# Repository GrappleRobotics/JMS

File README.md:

JMS
===
Another alternative Field Management System for the FIRST Robotics Competition.

JMS is based heavily off the official FRC FMS, as well as Cheesy-Arena. JMS differs in that the bulk of the network operations are performed onboard the JMS server itself, requiring minimal external and increasing the reliability of the system.

For those early-birds, do NOT install this on your personal machine. JMS WILL override your network, dhcp, and firewall settings. JMS is designed to be run on a Ubuntu Server 20.04 instance (either physical or in a VM).

More information coming soon.

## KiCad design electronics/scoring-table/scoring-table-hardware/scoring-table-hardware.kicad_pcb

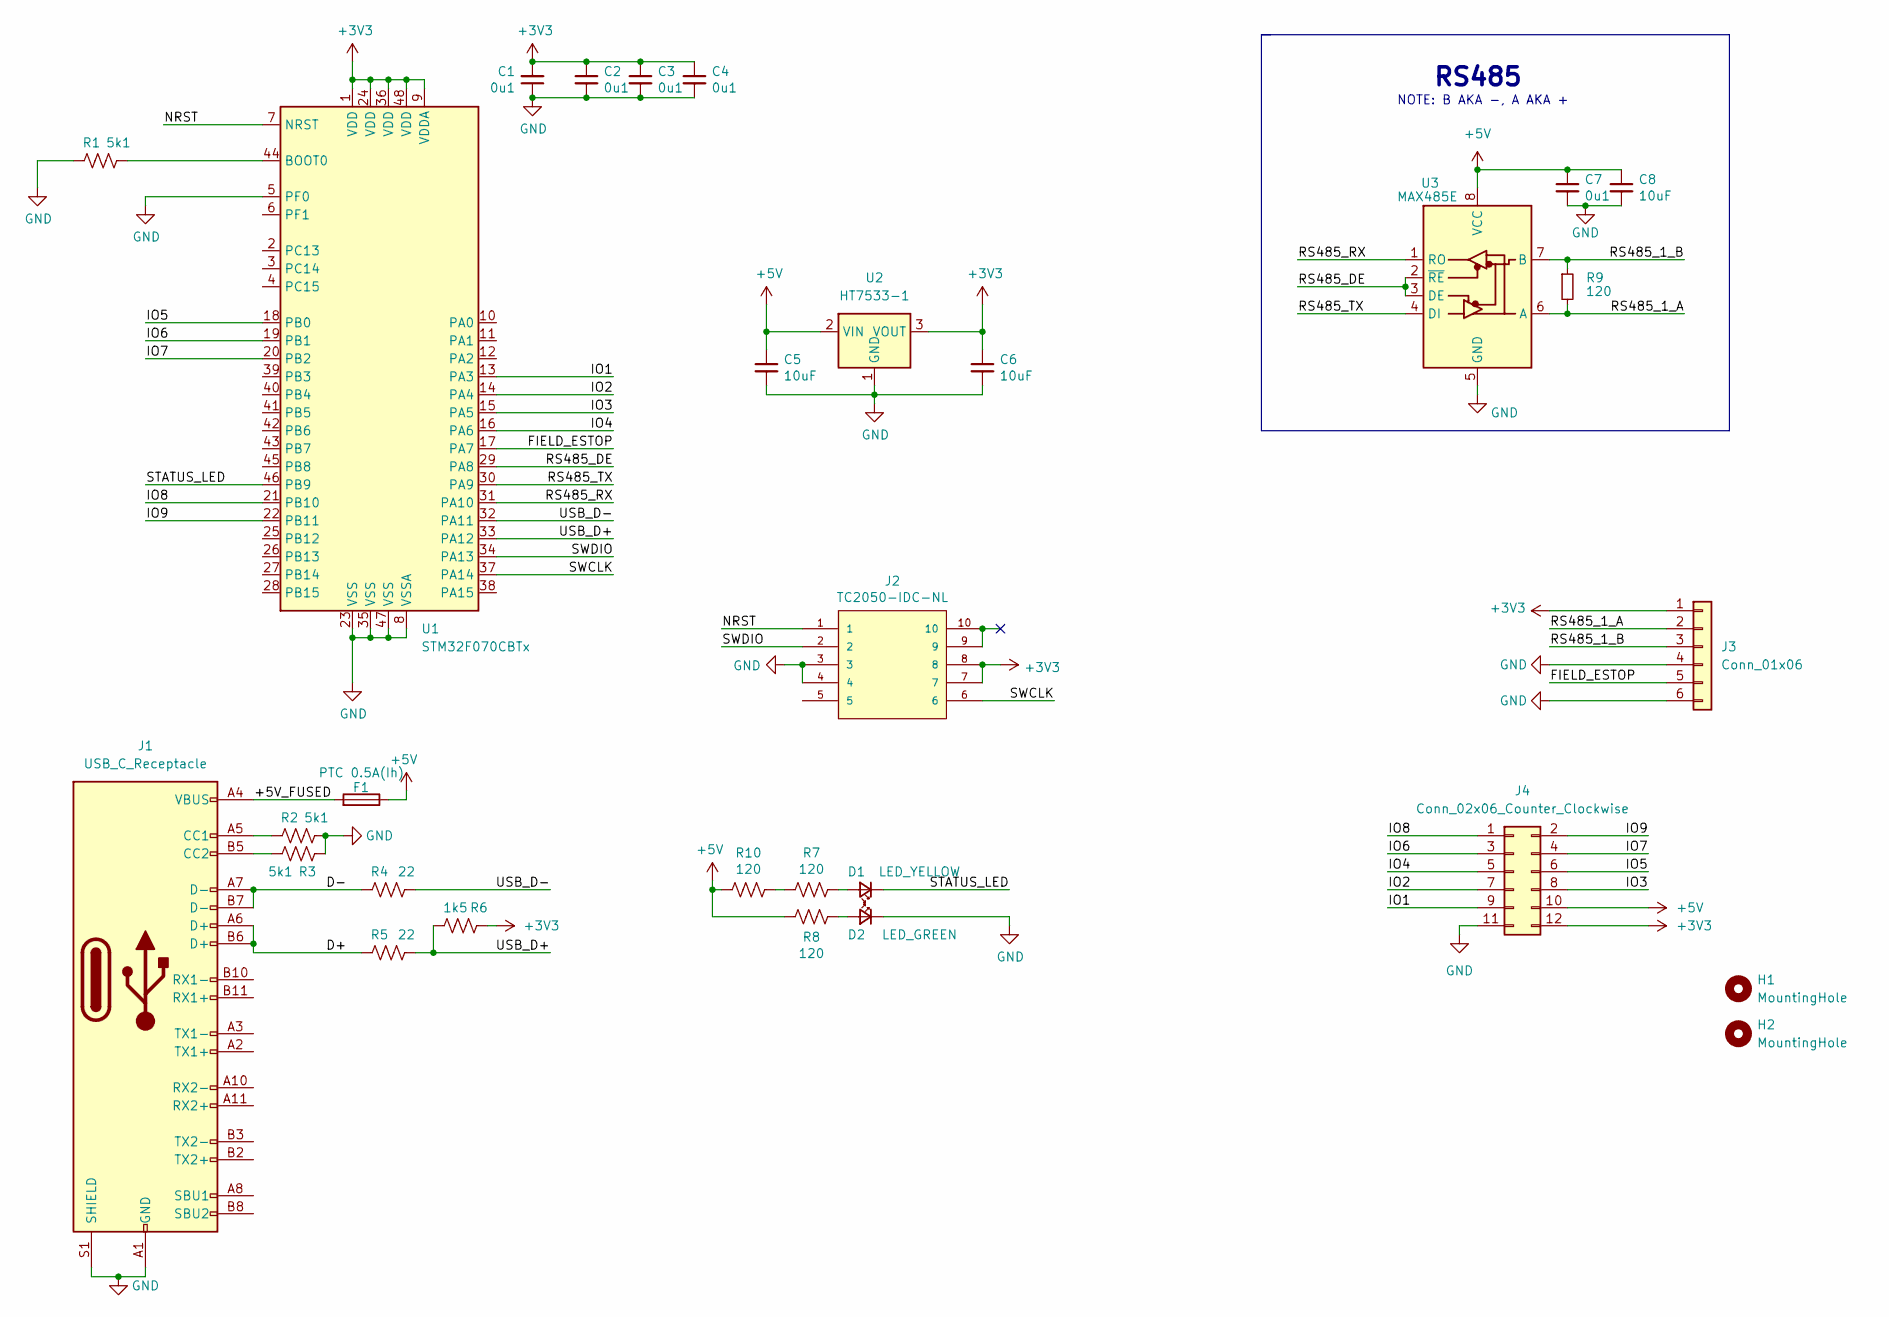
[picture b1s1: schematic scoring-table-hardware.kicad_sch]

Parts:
C1, C2, C3, C4, C7: 0u1; C_0603_1608Metric; LCSC C14663
C5, C6, C8: 10uF; C_0603_1608Metric; LCSC C96446
D1: LED_YELLOW; LED_0603_1608Metric; LCSC C72038
D2: LED_GREEN; LED_0603_1608Metric; LCSC C72043
F1: PTC 0.5A(Ih); Fuse_1206_3216Metric; LCSC C883126
H1, H2: MountingHole; MountingHole_3.2mm_M3
J1: USB_C_Receptacle; USB_C_Receptacle_Molex_105450-0101; LCSC C134092
J2: TC2050-IDC-NL; TAG-CONNECT_TC2050-IDC-NL; PARTREV A
J3: Conn_01x06; PhoenixContact_MC_1,5_6-G-5.08_1x06_P5.08mm_Horizontal; LCSC C505828
J4: Conn_02x06_Counter_Clockwise; PinHeader_2x06_P2.54mm_Vertical
R1, R2, R3: 5k1; R_0603_1608Metric; LCSC C23186
R4, R5: 22; R_0603_1608Metric; LCSC C23345
R6: 1k5; R_0603_1608Metric; LCSC C22843
R7, R8, R9, R10: 120; R_0603_1608Metric; LCSC C22787
U1: STM32F070CBTx; LQFP-48_7x7mm_P0.5mm; LCSC C74909
U2: HT7533-1; SOT-89-3; LCSC C14289
U3: MAX485E; SOIC-8_3.9x4.9mm_P1.27mm; LCSC C19738

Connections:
+3V3: C1.2, C2.1, C3.1, C4.1, C6.1, J2.7, J2.8, J3.1, J4.12, R6.2, U1.1 (VDD), U1.9 (VDDA), U1.24 (VDD), U1.36 (VDD), U1.48 (VDD), U2.3 (VOUT)
+5V: C5.1, C7.1, C8.1, F1.1, J4.10, R8.1, R10.1, U2.2 (VIN), U3.8 (VCC)
/+5V_FUSED: F1.2, J1.A4 (VBUS), J1.A9 (VBUS), J1.B4 (VBUS), J1.B9 (VBUS)
/D+: J1.A6 (D+), J1.B6 (D+), R5.2
/D-: J1.A7 (D-), J1.B7 (D-), R4.2
/FIELD_ESTOP: J3.5, U1.17 (PA7)
/IO1: J4.9, U1.13 (PA3)
/IO2: J4.7, U1.14 (PA4)
/IO3: J4.8, U1.15 (PA5)
/IO4: J4.5, U1.16 (PA6)
/IO5: J4.6, U1.18 (PB0)
/IO6: J4.3, U1.19 (PB1)
/IO7: J4.4, U1.20 (PB2)
/IO8: J4.1, U1.21 (PB10)
/IO9: J4.2, U1.22 (PB11)
/NRST: J2.1, U1.7 (NRST)
/RS485_1_A: J3.2, R9.2, U3.6 (A)
/RS485_1_B: J3.3, R9.1, U3.7 (B)
/RS485_DE: U1.29 (PA8), U3.2 (~RE), U3.3 (DE)
/RS485_RX: U1.31 (PA10), U3.1 (RO)
/RS485_TX: U1.30 (PA9), U3.4 (DI)
/STATUS_LED: D1.1 (K), U1.46 (PB9)
/SWCLK: J2.6, U1.37 (PA14)
/SWDIO: J2.2, U1.34 (PA13)
/USB_D+: R5.1, R6.1, U1.33 (PA12)
/USB_D-: R4.1, U1.32 (PA11)
GND: C1.1, C2.2, C3.2, C4.2, C5.2, C6.2, C7.2, C8.2, D2.1 (K), J1.A1 (GND), J1.A12 (GND), J1.B1 (GND), J1.B12 (GND), J1.S1 (SHIELD), J2.3, J2.4, J3.4, J3.6, J4.11, R1.2, R2.1, R3.2, U1.5 (PF0), U1.8 (VSSA), U1.23 (VSS), U1.35 (VSS), U1.47 (VSS), U2.1 (GND), U3.5 (GND)
unnamed: J1.A5 (CC1), R2.2
unnamed: J1.B5 (CC2), R3.1
unnamed: R7.1, R10.2
unnamed: D1.2 (A), R7.2
unnamed: D2.2 (A), R8.2
unnamed: R1.1, U1.44 (BOOT0)

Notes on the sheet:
RS485
NOTE: B AKA -, A AKA +

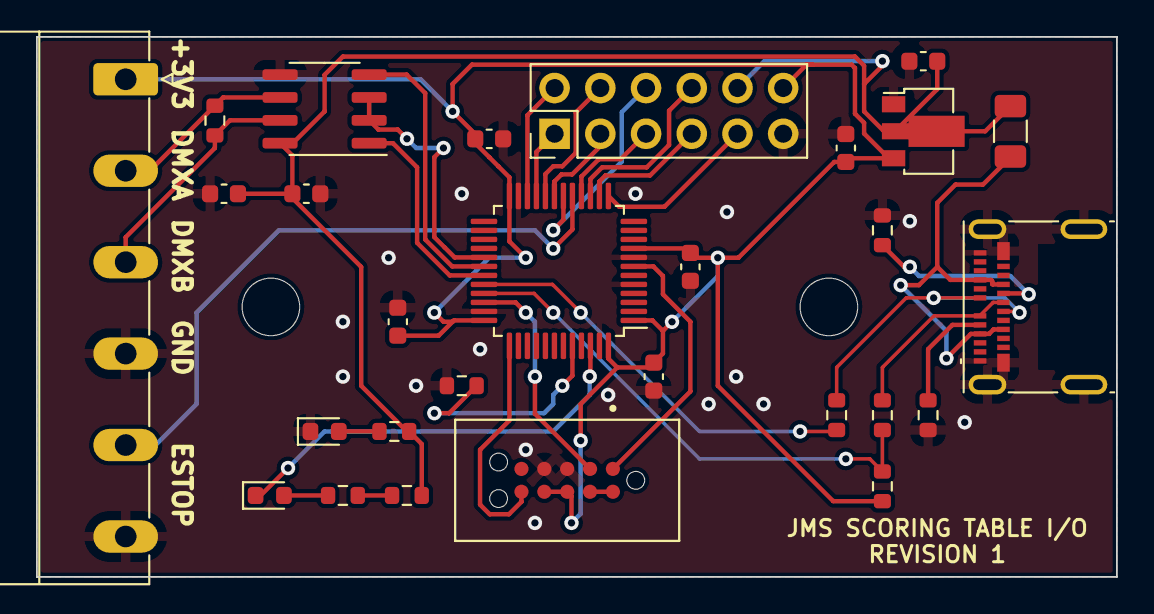
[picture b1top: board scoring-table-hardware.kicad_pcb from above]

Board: 2 copper layers, 60.0 x 30.0 mm, 30 parts (0 on the bottom side), 33 nets.

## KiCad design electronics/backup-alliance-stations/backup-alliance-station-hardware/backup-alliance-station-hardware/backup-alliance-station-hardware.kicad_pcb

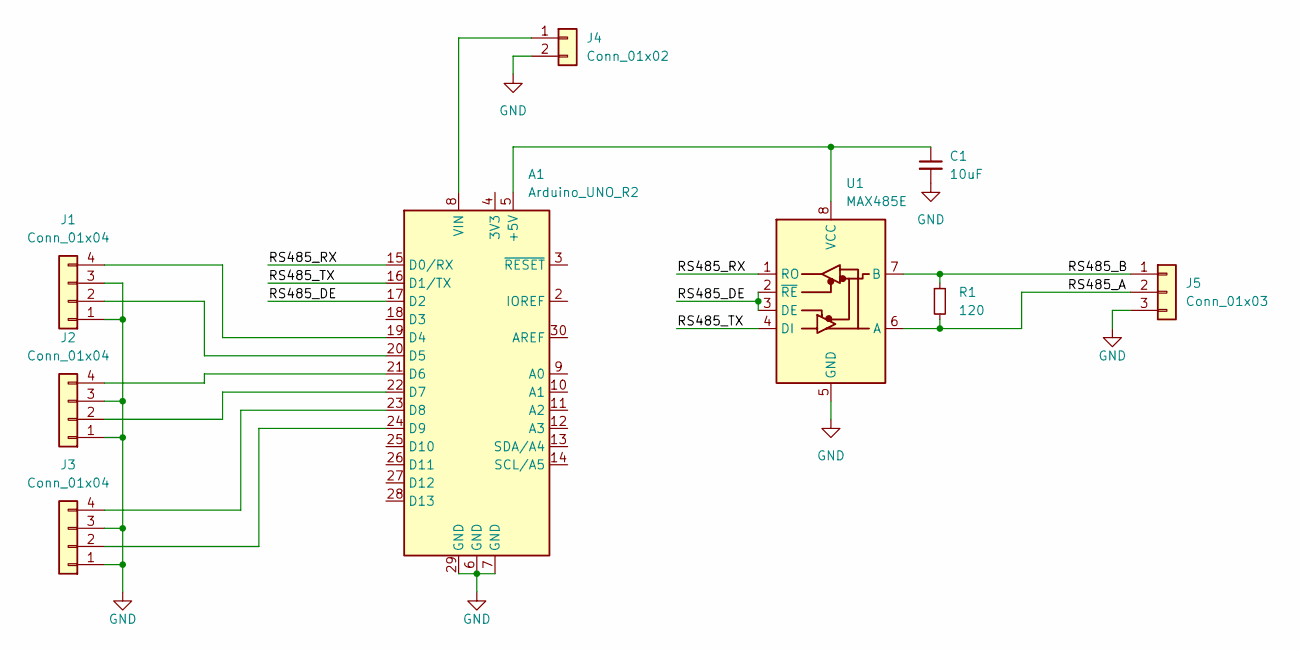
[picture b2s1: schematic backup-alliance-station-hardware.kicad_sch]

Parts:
A1: Arduino_UNO_R2
C1: 10uF; C_Disc_D4.7mm_W2.5mm_P5.00mm
J1, J2, J3: Conn_01x04; TerminalBlock_Phoenix_PT-1,5-4-3.5-H_1x04_P3.50mm_Horizontal
J4: Conn_01x02; TerminalBlock_Phoenix_PT-1,5-2-3.5-H_1x02_P3.50mm_Horizontal
J5: Conn_01x03; TerminalBlock_Phoenix_PT-1,5-3-3.5-H_1x03_P3.50mm_Horizontal
R1: 120; R_Axial_DIN0207_L6.3mm_D2.5mm_P7.62mm_Horizontal
U1: MAX485E; DIP-8_W7.62mm

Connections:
/RS485_A: J5.2, R1.2, U1.6 (A)
/RS485_B: J5.1, R1.1, U1.7 (B)
/RS485_DE: A1.17 (D2), U1.2 (~RE), U1.3 (DE)
/RS485_RX: A1.15 (D0/RX), U1.1 (RO)
/RS485_TX: A1.16 (D1/TX), U1.4 (DI)
GND: A1.6 (GND), A1.7 (GND), A1.29 (GND), C1.2, J1.1, J1.3, J2.1, J2.3, J3.1, J3.3, J4.2, J5.3, U1.5 (GND)
unnamed: A1.5 (+5V), C1.1, U1.8 (VCC)
unnamed: A1.8 (VIN), J4.1
unnamed: A1.19 (D4), J1.4
unnamed: A1.20 (D5), J1.2
unnamed: A1.21 (D6), J2.4
unnamed: A1.22 (D7), J2.2
unnamed: A1.23 (D8), J3.4
unnamed: A1.24 (D9), J3.2

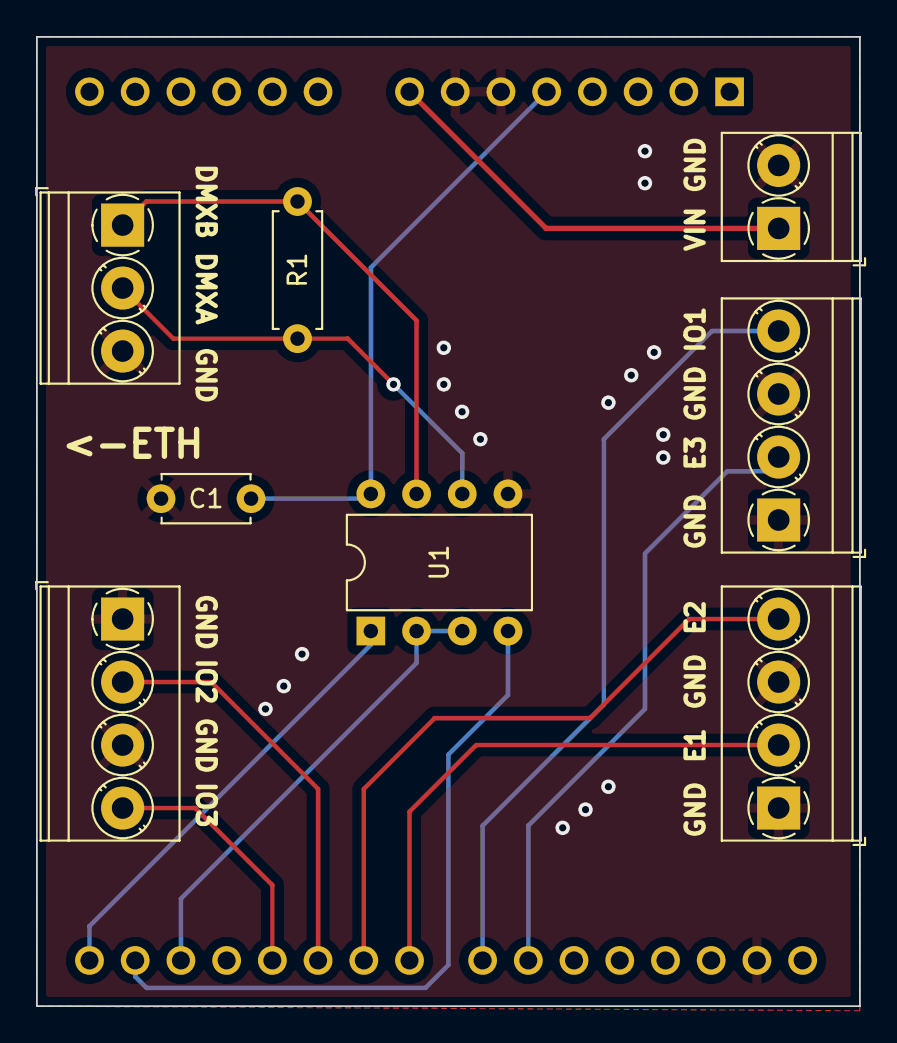
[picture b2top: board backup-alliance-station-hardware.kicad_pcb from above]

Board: 2 copper layers, 45.7 x 53.8 mm, 9 parts (1 on the bottom side), 14 nets.

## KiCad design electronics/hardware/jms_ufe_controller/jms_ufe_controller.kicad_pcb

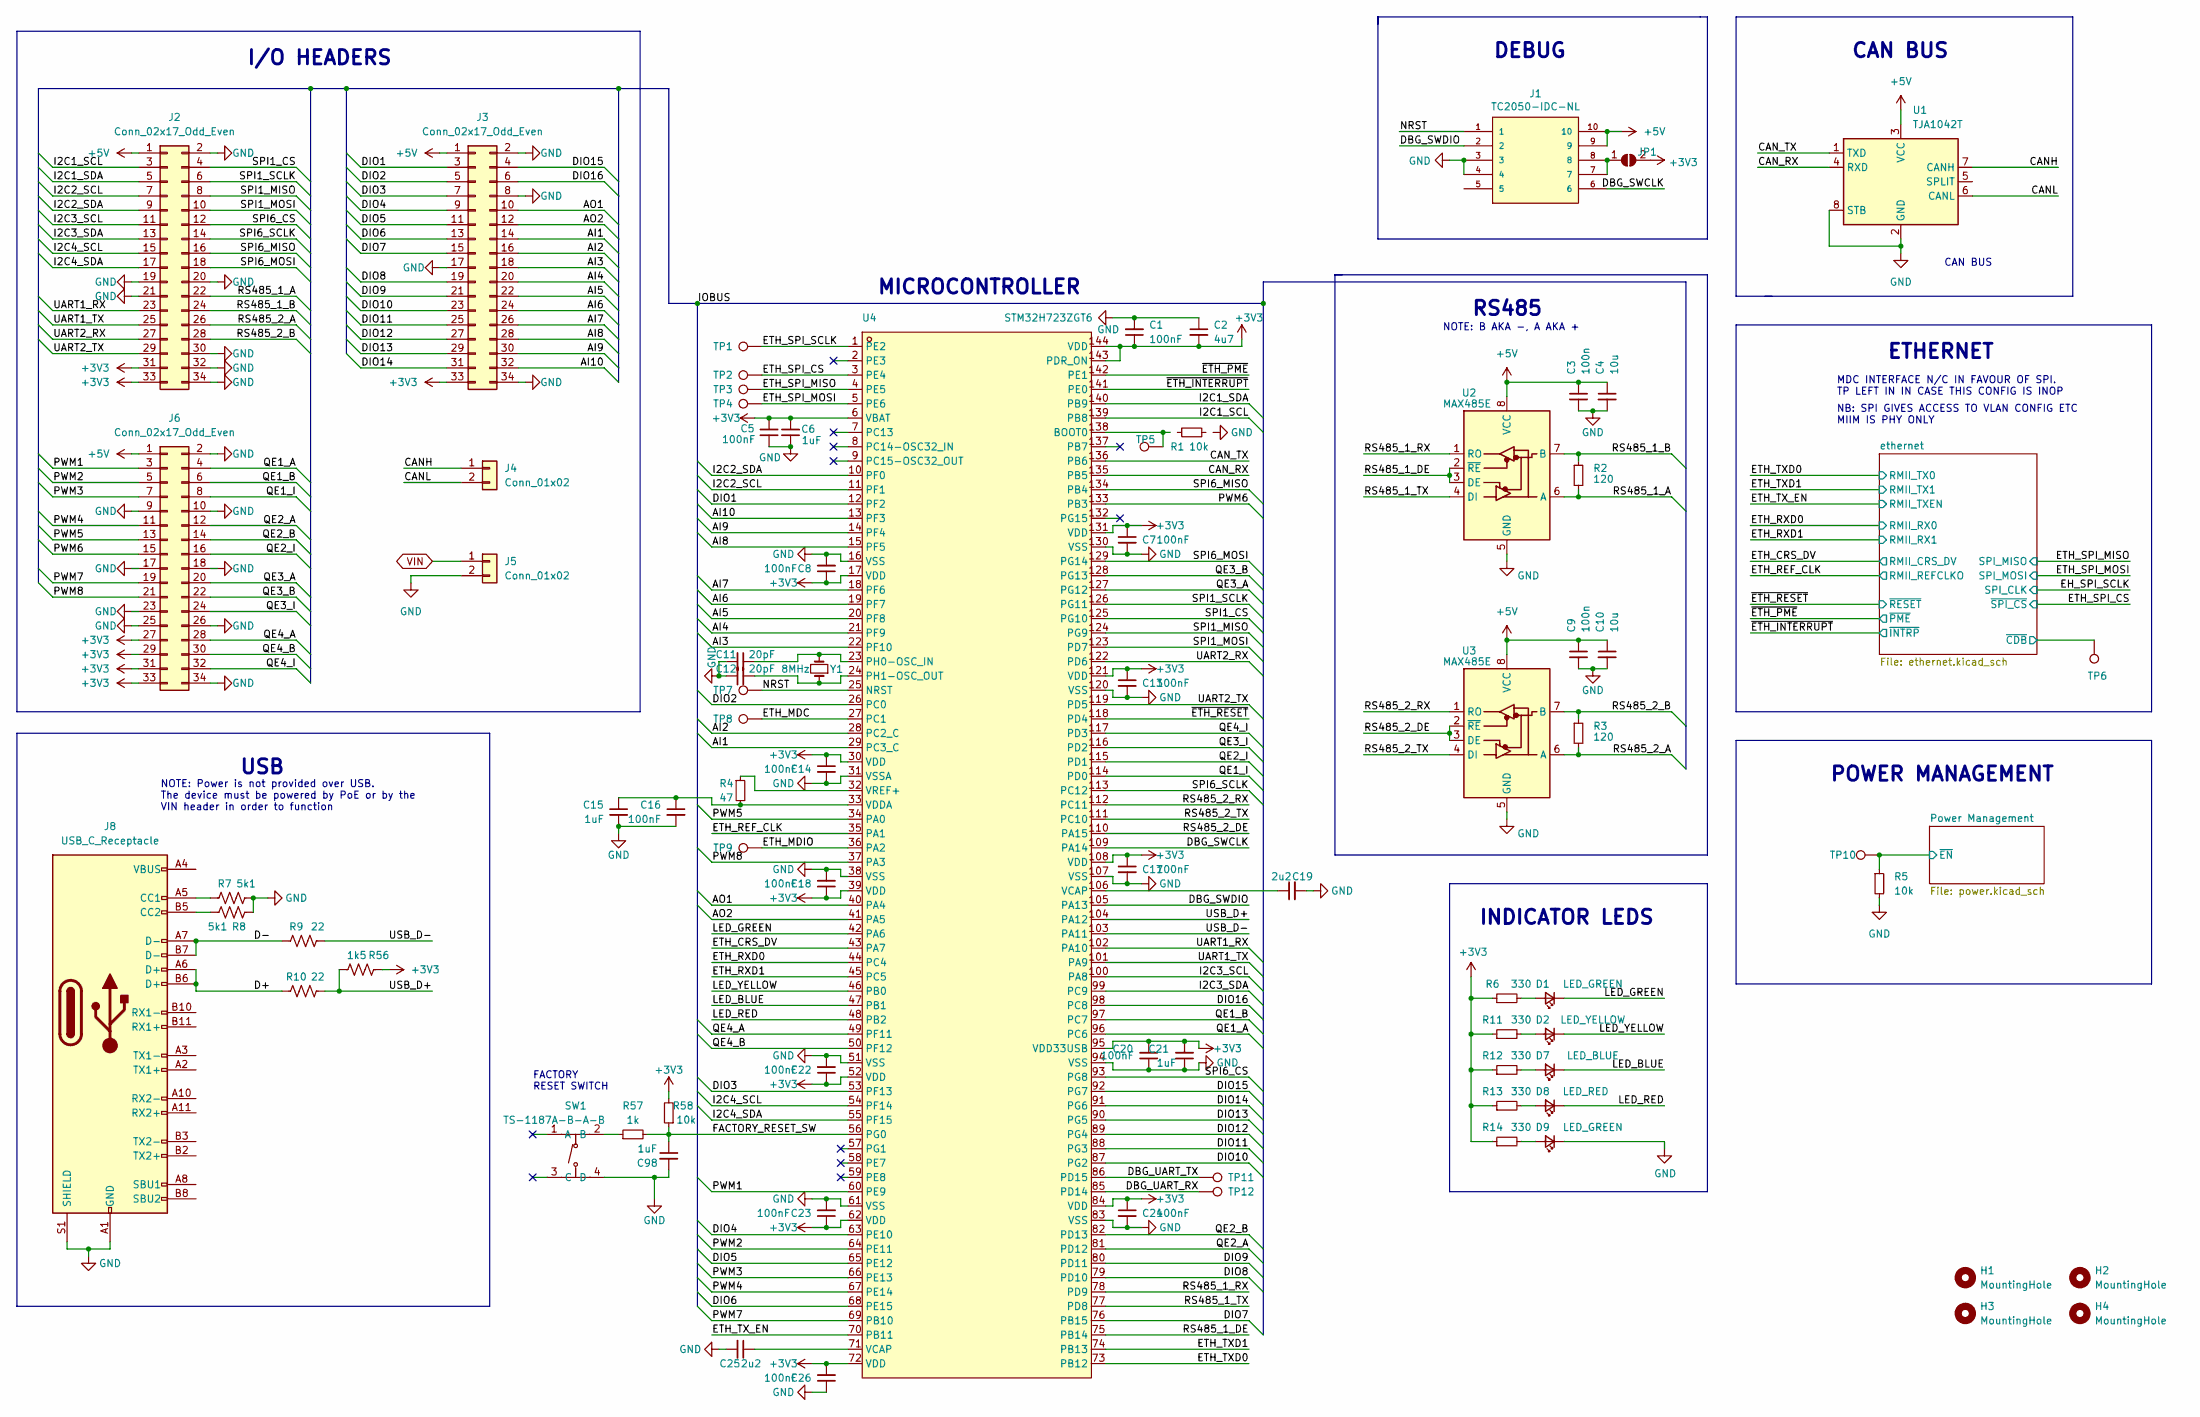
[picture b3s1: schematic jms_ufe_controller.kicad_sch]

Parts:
C1, C5, C7, C8, C13, C14, C16, C17, C18, C20, C22, C23, C24, C26: 100nF; C_0402_1005Metric
C2: 4u7; C_0402_1005Metric
C3, C9: 100n; C_0402_1005Metric
C4, C10: 10u; C_0402_1005Metric
C6, C15, C21, C98: 1uF; C_0402_1005Metric
C11, C12: 20pF; C_0402_1005Metric
C19, C25: 2u2; C_0402_1005Metric
D1, D9: LED_GREEN; LED_0603_1608Metric; LCSC C72043
D2: LED_YELLOW; LED_0603_1608Metric; LCSC C72038
D7: LED_BLUE; LED_0603_1608Metric; LCSC C72041
D8: LED_RED; LED_0603_1608Metric; LCSC C2286
H1, H2, H3, H4: MountingHole; MountingHole_3.2mm_M3
J1: TC2050-IDC-NL; TAG-CONNECT_TC2050-IDC-NL; PARTREV A
J2, J3, J6: Conn_02x17_Odd_Even; PinHeader_2x17_P2.54mm_Vertical
J4, J5: Conn_01x02; TerminalBlock_Phoenix_PT-1,5-2-3.5-H_1x02_P3.50mm_Horizontal
J8: USB_C_Receptacle; USB_C_Receptacle_Molex_105450-0101
JP1: SolderJumper_2_Open; SolderJumper-2_P1.3mm_Open_TrianglePad1.0x1.5mm
R1, R5, R58: 10k; R_0402_1005Metric
R2, R3: 120; R_0402_1005Metric
R4: 47; R_0402_1005Metric
R6, R11, R12, R13, R14: 330; R_0402_1005Metric
R7, R8: 5k1; R_0402_1005Metric
R9, R10: 22; R_0402_1005Metric
R56: 1k5; R_0402_1005Metric
R57: 1k; R_0402_1005Metric
SW1: TS-1187A-B-A-B; SW-SMD_4P-L5.1-W5.1-P3.70-LS6.5-TL-2; LCSC Part C318884
TP1, TP2, TP3, TP4, TP5, TP6, TP7, TP8, TP9, TP10, TP11, TP12: TestPoint; TestPoint_Pad_1.5x1.5mm
U1: TJA1042T; SOIC-8_3.9x4.9mm_P1.27mm; LCSC C53670
U2, U3: MAX485E; SOIC-8_3.9x4.9mm_P1.27mm; LCSC C19738
U4: STM32H723ZGT6; LQFP-144_L20.0-W20.0-P0.50-LS22.0-BL; LCSC Part C730146
Y1: 8MHz; Crystal_SMD_5032-2Pin_5.0x3.2mm; LCSC C115962

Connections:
+3V3: C1.1, C2.2, C5.2, C6.2, C7.1, C8.1, C13.1, C14.1, C17.1, C18.1, C20.2, C21.2, C22.1, C23.1, C24.1, C26.2, J2.31, J2.33, J3.33, J6.27, J6.29, J6.31, J6.33, JP1.2 (B), R6.1, R11.1, R12.1, R13.1, R14.1, R56.2, R58.2, U4.6 (VBAT), U4.17 (VDD), U4.30 (VDD), U4.39 (VDD), U4.52 (VDD), U4.62 (VDD), U4.72 (VDD), U4.84 (VDD), U4.95 (VDD33USB), U4.108 (VDD), U4.121 (VDD), U4.131 (VDD), U4.143 (PDR_ON), U4.144 (VDD); also elsewhere on the board
+5V: C3.1, C4.1, C9.1, C10.1, J1.9, J1.10, J2.1, J3.1, J6.1, U1.3 (VCC), U2.8 (VCC), U3.8 (VCC); also elsewhere on the board
/AI1: J3.14, U4.29 (PC3_C)
/AI2: J3.16, U4.28 (PC2_C)
/AI3: J3.18, U4.22 (PF10)
/AI4: J3.20, U4.21 (PF9)
/AI5: J3.22, U4.20 (PF8)
/AI6: J3.24, U4.19 (PF7)
/AI7: J3.26, U4.18 (PF6)
/AI8: J3.28, U4.15 (PF5)
/AI9: J3.30, U4.14 (PF4)
/AI10: J3.32, U4.13 (PF3)
/AO1: J3.10, U4.40 (PA4)
/AO2: J3.12, U4.41 (PA5)
/CANH: J4.1, U1.7 (CANH)
/CANL: J4.2, U1.6 (CANL)
/CAN_RX: U1.4 (RXD), U4.135 (PB5)
/CAN_TX: U1.1 (TXD), U4.136 (PB6)
/D+: J8.A6 (D+), J8.B6 (D+), R10.2
/D-: J8.A7 (D-), J8.B7 (D-), R9.2
/DBG_SWCLK: J1.6, U4.109 (PA14)
/DBG_SWDIO: J1.2, U4.105 (PA13)
/DBG_UART_RX: TP12.1, U4.85 (PD14)
/DBG_UART_TX: TP11.1, U4.86 (PD15)
/DIO1: J3.3, U4.12 (PF2)
/DIO2: J3.5, U4.26 (PC0)
/DIO3: J3.7, U4.53 (PF13)
/DIO4: J3.9, U4.63 (PE10)
/DIO5: J3.11, U4.65 (PE12)
/DIO6: J3.13, U4.68 (PE15)
/DIO7: J3.15, U4.76 (PB15)
/DIO8: J3.19, U4.79 (PD10)
/DIO9: J3.21, U4.80 (PD11)
/DIO10: J3.23, U4.87 (PG2)
/DIO11: J3.25, U4.88 (PG3)
/DIO12: J3.27, U4.89 (PG4)
/DIO13: J3.29, U4.90 (PG5)
/DIO14: J3.31, U4.91 (PG6)
/DIO15: J3.4, U4.92 (PG7)
/DIO16: J3.6, U4.98 (PC8)
/ETH_CRS_DV: U4.43 (PA7); also elsewhere on the board
/ETH_MDC: TP8.1, U4.27 (PC1)
/ETH_MDIO: TP9.1, U4.36 (PA2)
/ETH_REF_CLK: U4.35 (PA1); also elsewhere on the board
/ETH_RXD0: U4.44 (PC4); also elsewhere on the board
/ETH_RXD1: U4.45 (PC5); also elsewhere on the board
/ETH_SPI_CS: TP2.1, U4.3 (PE4); also elsewhere on the board
/ETH_SPI_MISO: TP3.1, U4.4 (PE5); also elsewhere on the board
/ETH_SPI_MOSI: TP4.1, U4.5 (PE6); also elsewhere on the board
/ETH_SPI_SCLK: TP1.1, U4.1 (PE2)
/ETH_TXD0: U4.73 (PB12); also elsewhere on the board
/ETH_TXD1: U4.74 (PB13); also elsewhere on the board
/ETH_TX_EN: U4.70 (PB11); also elsewhere on the board
/FACTORY_RESET_SW: C98.1, R57.2, R58.1, U4.56 (PG0)
/I2C1_SCL: J2.3, U4.139 (PB8)
/I2C1_SDA: J2.5, U4.140 (PB9)
/I2C2_SCL: J2.7, U4.11 (PF1)
/I2C2_SDA: J2.9, U4.10 (PF0)
/I2C3_SCL: J2.11, U4.100 (PA8)
/I2C3_SDA: J2.13, U4.99 (PC9)
/I2C4_SCL: J2.15, U4.54 (PF14)
/I2C4_SDA: J2.17, U4.55 (PF15)
/LED_BLUE: D7.1 (K), U4.47 (PB1)
/LED_GREEN: D1.1 (K), U4.42 (PA6)
/LED_RED: D8.1 (K), U4.48 (PB2)
/LED_YELLOW: D2.1 (K), U4.46 (PB0)
/NRST: J1.1, TP7.1, U4.25 (NRST)
/PWM1: J6.3, U4.60 (PE9)
/PWM2: J6.5, U4.64 (PE11)
/PWM3: J6.7, U4.66 (PE13)
/PWM4: J6.11, U4.67 (PE14)
/PWM5: J6.13, U4.34 (PA0)
/PWM6: J6.15, U4.133 (PB3)
/PWM7: J6.19, U4.69 (PB10)
/PWM8: J6.21, U4.37 (PA3)
/Power Management/~EN: R5.1, TP10.1; also elsewhere on the board
/QE1_A: J6.4, U4.96 (PC6)
/QE1_B: J6.6, U4.97 (PC7)
/QE1_I: J6.8, U4.114 (PD0)
/QE2_A: J6.12, U4.81 (PD12)
/QE2_B: J6.14, U4.82 (PD13)
/QE2_I: J6.16, U4.115 (PD1)
/QE3_A: J6.20, U4.127 (PG12)
/QE3_B: J6.22, U4.128 (PG13)
/QE3_I: J6.24, U4.116 (PD2)
/QE4_A: J6.28, U4.49 (PF11)
/QE4_B: J6.30, U4.50 (PF12)
/QE4_I: J6.32, U4.117 (PD3)
/RS485_1_A: J2.22, R2.2, U2.6 (A)
/RS485_1_B: J2.24, R2.1, U2.7 (B)
/RS485_1_DE: U2.2 (~RE), U2.3 (DE), U4.75 (PB14)
/RS485_1_RX: U2.1 (RO), U4.78 (PD9)
/RS485_1_TX: U2.4 (DI), U4.77 (PD8)
/RS485_2_A: J2.26, R3.2, U3.6 (A)
/RS485_2_B: J2.28, R3.1, U3.7 (B)
/RS485_2_DE: U3.2 (~RE), U3.3 (DE), U4.110 (PA15)
/RS485_2_RX: U3.1 (RO), U4.112 (PC11)
/RS485_2_TX: U3.4 (DI), U4.111 (PC10)
/SPI1_CS: J2.4, U4.125 (PG10)
/SPI1_MISO: J2.8, U4.124 (PG9)
/SPI1_MOSI: J2.10, U4.123 (PD7)
/SPI1_SCLK: J2.6, U4.126 (PG11)
/SPI6_CS: J2.12, U4.93 (PG8)
/SPI6_MISO: J2.16, U4.134 (PB4)
/SPI6_MOSI: J2.18, U4.129 (PG14)
/SPI6_SCLK: J2.14, U4.113 (PC12)
/UART1_RX: J2.23, U4.102 (PA10)
/UART1_TX: J2.25, U4.101 (PA9)
/UART2_RX: J2.27, U4.122 (PD6)
/UART2_TX: J2.29, U4.119 (PD5)
/USB_D+: R10.1, R56.1, U4.104 (PA12)
/USB_D-: R9.1, U4.103 (PA11)
/ethernet/~CDB: TP6.1; also elsewhere on the board
/~ETH_INTERRUPT: U4.141 (PE0); also elsewhere on the board
/~ETH_PME: U4.142 (PE1); also elsewhere on the board
/~ETH_RESET: U4.118 (PD4); also elsewhere on the board
GND: C1.2, C2.1, C3.2, C4.2, C5.1, C6.1, C7.2, C8.2, C9.2, C10.2, C11.2, C12.2, C13.2, C14.2, C15.2, C16.2, C17.2, C18.2, C19.2, C20.1, C21.1, C22.2, C23.2, C24.2, C25.2, C26.1, C98.2, D9.1 (K), J1.3, J1.4, J2.2, J2.19, J2.20, J2.21, J2.30, J2.32, J2.34, J3.2, J3.8, J3.17, J3.34, J5.2, J6.2, J6.9, J6.10, J6.17, J6.18, J6.23, J6.25, J6.26, J6.34, J8.A1 (GND), J8.A12 (GND), J8.B1 (GND), J8.B12 (GND), J8.S1 (SHIELD), R5.2, R7.1, R8.2, SW1.4 (D), U1.2 (GND), U1.8 (STB), U2.5 (GND), U3.5 (GND), U4.16 (VSS), U4.31 (VSSA), U4.38 (VSS), U4.51 (VSS), U4.61 (VSS), U4.83 (VSS), U4.94 (VSS), U4.107 (VSS), U4.120 (VSS), U4.130 (VSS); also elsewhere on the board
unnamed: C11.1, U4.23 (PH0-OSC_IN), Y1.2
unnamed: C12.1, U4.24 (PH1-OSC_OUT), Y1.1
unnamed: C15.1, C16.1, R4.2, U4.33 (VDDA)
unnamed: C19.1, U4.106 (VCAP)
unnamed: C25.1, U4.71 (VCAP)
unnamed: D1.2 (A), R6.2
unnamed: D2.2 (A), R11.2
unnamed: D7.2 (A), R12.2
unnamed: D8.2 (A), R13.2
unnamed: D9.2 (A), R14.2
unnamed: J1.7, J1.8, JP1.1 (A)
unnamed: J8.A4 (VBUS), J8.A9 (VBUS), J8.B4 (VBUS), J8.B9 (VBUS)
unnamed: J8.A5 (CC1), R7.2
unnamed: J8.B5 (CC2), R8.1
unnamed: R4.1, U4.32 (VREF+)
unnamed: R57.1, SW1.2 (B)
unnamed: TP5.1, U4.138 (BOOT0)
VIN: J5.1; also elsewhere on the board

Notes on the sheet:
USB
NOTE: Power is not provided over USB. The device must be powered by PoE or by the VIN header in order to function
CAN BUS
INDICATOR LEDS
ETHERNET
NB: SPI GIVES ACCESS TO VLAN CONFIG ETC MIIM IS PHY ONLY
DEBUG
POWER MANAGEMENT
RS485
I/O HEADERS
MICROCONTROLLER
CAN BUS
MDC INTERFACE N/C IN FAVOUR OF SPI. TP LEFT IN IN CASE THIS CONFIG IS INOP
FACTORY RESET SWITCH
NOTE: B AKA -, A AKA +

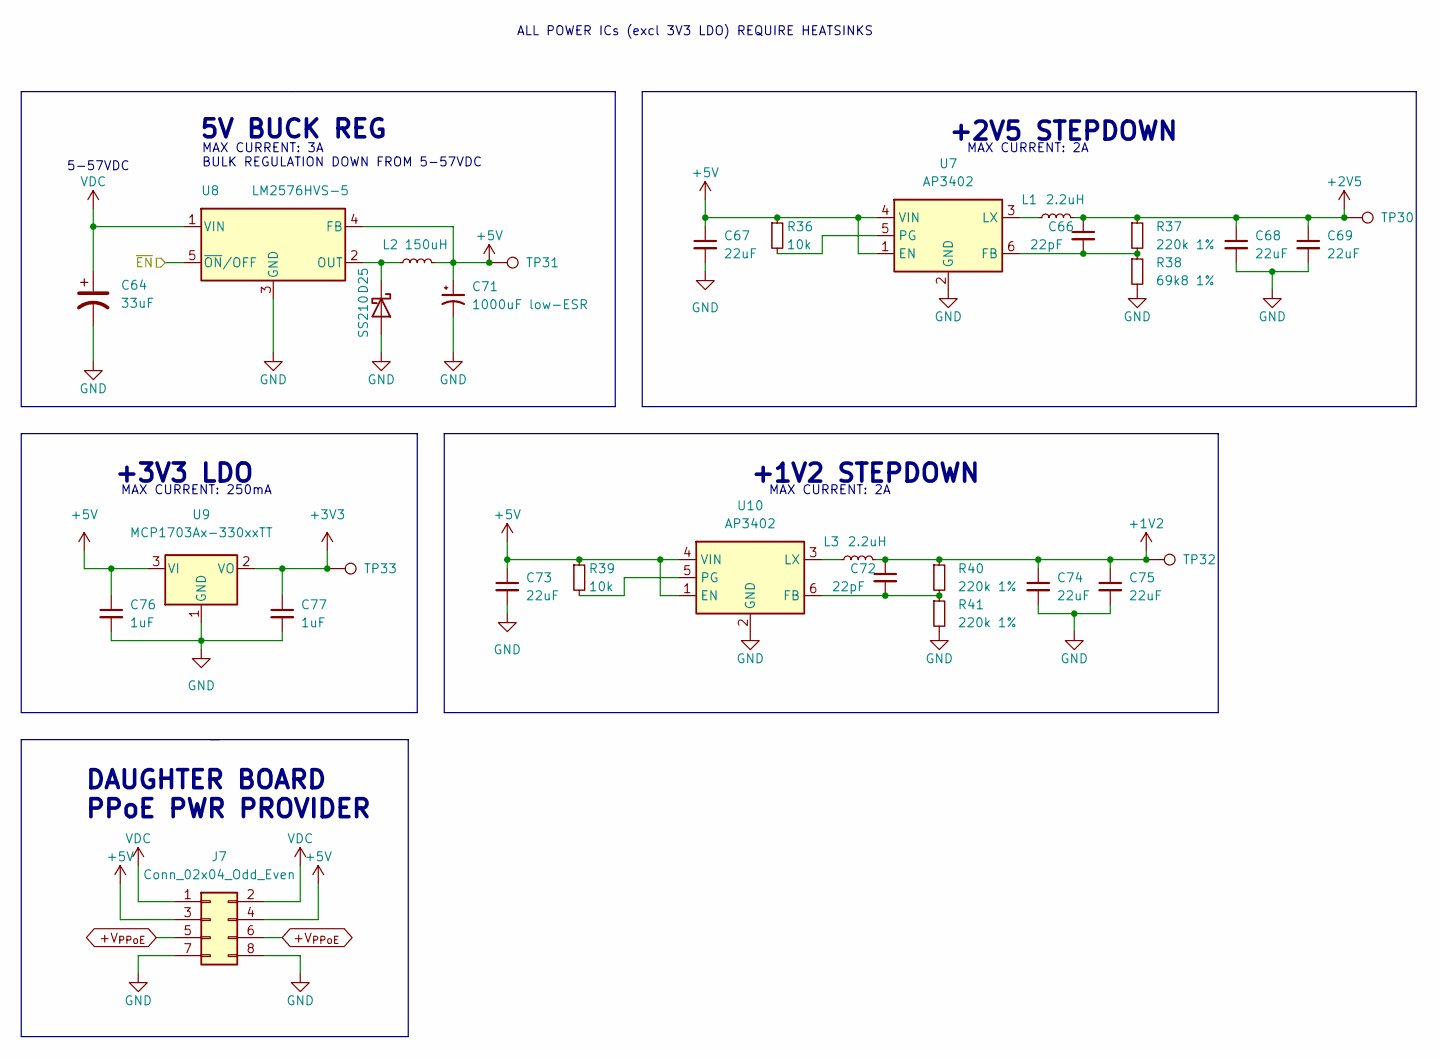
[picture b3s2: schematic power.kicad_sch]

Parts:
C64: 33uF; CP_Radial_D16.0mm_P7.50mm; LCSC C116223
C66, C72: 22pF; C_0402_1005Metric
C67, C68, C69, C73, C74, C75: 22uF; C_0402_1005Metric
C71: 1000uF low-ESR; CP_Radial_D12.5mm_P5.00mm; LCSC C250981
C76, C77: 1uF; C_0402_1005Metric
D25: SS210; D_SMA; LCSC C14996
J7: Conn_02x04_Odd_Even; PinHeader_2x04_P2.54mm_Vertical
L1, L3: 2.2uH; L_1008_2520Metric; LCSC C602014
L2: 150uH; L_12x12mm_H8mm; Digikey SRR1210-151M
R36, R39: 10k; R_0402_1005Metric
R37, R40, R41: 220k 1%; R_0402_1005Metric
R38: 69k8 1%; R_0402_1005Metric
TP30, TP31, TP32, TP33: TestPoint; TestPoint_Pad_1.5x1.5mm
U7, U10: AP3402; TSOT-23-6
U8: LM2576HVS-5; TO-263-5_TabPin3
U9: MCP1703Ax-330xxTT; SOT-23; LCSC C144183

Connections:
+1V2: C72.1, C74.1, C75.1, L3.2, R40.1, TP32.1; also elsewhere on the board
+2V5: C66.1, C68.1, C69.1, L1.2, R37.1, TP30.1; also elsewhere on the board
+3V3: C77.1, TP33.1, U9.2 (VO); also elsewhere on the board
+5V: C67.1, C71.1, C73.1, C76.1, J7.3, J7.4, L2.2, R36.1, R39.1, TP31.1, U7.1 (EN), U7.4 (VIN), U8.4 (FB), U9.3 (VI), U10.1 (EN), U10.4 (VIN); also elsewhere on the board
+V_{PPoE}: J7.5, J7.6; also elsewhere on the board
/Power Management/~EN: U8.5 (~ON/OFF); also elsewhere on the board
GND: C64.2, C67.2, C68.2, C69.2, C71.2, C73.2, C74.2, C75.2, C76.2, C77.2, D25.2 (A), J7.7, J7.8, R38.2, R41.2, U7.2 (GND), U8.3 (GND), U9.1 (GND), U10.2 (GND); also elsewhere on the board
unnamed: C66.2, R37.2, R38.1, U7.6 (FB)
unnamed: C72.2, R40.2, R41.1, U10.6 (FB)
unnamed: D25.1 (K), L2.1, U8.2 (OUT)
unnamed: L1.1, U7.3 (LX)
unnamed: L3.1, U10.3 (LX)
unnamed: R36.2, U7.5 (PG)
unnamed: R39.2, U10.5 (PG)
VDC: C64.1, J7.1, J7.2, U8.1 (VIN); also elsewhere on the board

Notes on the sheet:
5-57VDC
MAX CURRENT: 250mA
+3V3 LDO
DAUGHTER BOARD PPoE PWR PROVIDER
BULK REGULATION DOWN FROM 5-57VDC
+2V5 STEPDOWN
5V BUCK REG
ALL POWER ICs (excl 3V3 LDO) REQUIRE HEATSINKS
+1V2 STEPDOWN
MAX CURRENT: 2A
MAX CURRENT: 3A

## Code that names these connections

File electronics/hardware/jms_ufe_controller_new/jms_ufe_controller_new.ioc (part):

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Mcu.Name=STM32H723ZGTx
Mcu.Package=LQFP144
Mcu.UserName=STM32H723ZGTx
PA0.GPIOParameters=GPIO_Label
PA0.GPIO_Label=PWM5
PA0.Signal=S_TIM2_CH1_ETR
PA1.Mode=RMII
PA1.Signal=ETH_REF_CLK
PA10.GPIOParameters=GPIO_Label
PA10.GPIO_Label=UART1_RX
PA10.Mode=Asynchronous
PA10.Signal=USART1_RX
PA11.GPIOParameters=GPIO_Label
PA11.GPIO_Label=USB_D-
PA11.Mode=Device_Only_FS
PA11.Signal=USB_OTG_HS_DM
PA12.GPIOParameters=GPIO_Label
PA12.GPIO_Label=USB_D+
PA12.Mode=Device_Only_FS
PA12.Signal=USB_OTG_HS_DP
PA13(JTMS/SWDIO).Mode=Serial_Wire
PA13(JTMS/SWDIO).Signal=DEBUG_JTMS-SWDIO
PA14(JTCK/SWCLK).Mode=Serial_Wire
PA14(JTCK/SWCLK).Signal=DEBUG_JTCK-SWCLK
PA15(JTDI).GPIOParameters=GPIO_Label
PA15(JTDI).GPIO_Label=RS485_2_DE
PA15(JTDI).Mode=Hardware Flow Control (RS485)
PA15(JTDI).Signal=UART4_DE
PA2.Mode=RMII
PA2.Signal=ETH_MDIO
PA3.GPIOParameters=GPIO_Label
PA3.GPIO_Label=PWM8
PA3.Signal=S_TIM2_CH4
PA4.GPIOParameters=GPIO_Label
PA4.GPIO_Label=AO1
PA4.Signal=COMP_DAC11_group
PA5.GPIOParameters=GPIO_Label
PA5.GPIO_Label=AO2
PA5.Signal=COMP_DAC12_group
PA6.GPIOParameters=GPIO_Label
PA6.GPIO_Label=LED_GRN
PA6.Signal=GPIO_Output
PA7.Mode=RMII
PA7.Signal=ETH_CRS_DV
PA8.Mode=I2C
PA8.Signal=I2C3_SCL
PA9.GPIOParameters=GPIO_Label
PA9.GPIO_Label=UART1_TX
PA9.Mode=Asynchronous
PA9.Signal=USART1_TX
PB0.GPIOParameters=GPIO_Label
PB0.GPIO_Label=LED_YEL
PB0.Signal=GPIO_Output
PB1.GPIOParameters=GPIO_Label
PB1.GPIO_Label=LED_BLU
PB1.Signal=GPIO_Output
PB10.GPIOParameters=GPIO_Label
PB10.GPIO_Label=PWM7
PB10.Signal=S_TIM2_CH3
PB11.Mode=RMII
PB11.Signal=ETH_TX_EN
PB12.Mode=RMII
PB12.Signal=ETH_TXD0
PB13.Mode=RMII
PB13.Signal=ETH_TXD1
PB14.GPIOParameters=GPIO_Label
PB14.GPIO_Label=RS485_1_DE
PB14.Mode=Hardware Flow Control (RS485)
PB14.Signal=USART3_DE
PB15.GPIOParameters=GPIO_Label
PB15.GPIO_Label=DIO7
PB15.Signal=GPIO_Output
PB2.GPIOParameters=GPIO_Label
PB2.GPIO_Label=LED_RED
PB2.Signal=GPIO_Output
PB3(JTDO/TRACESWO).GPIOParameters=GPIO_Label
PB3(JTDO/TRACESWO).GPIO_Label=PWM6
PB3(JTDO/TRACESWO).Signal=S_TIM2_CH2
PB4(NJTRST).Mode=Full_Duplex_Master
PB4(NJTRST).Signal=SPI6_MISO
PB5.GPIOParameters=GPIO_Label
PB5.GPIO_Label=CAN_RX
PB5.Mode=FDCAN_Activate
PB5.Signal=FDCAN2_RX
PB6.GPIOParameters=GPIO_Label
PB6.GPIO_Label=CAN_TX
PB6.Mode=FDCAN_Activate
PB6.Signal=FDCAN2_TX
PB8.Mode=I2C
PB8.Signal=I2C1_SCL
PB9.Mode=I2C
PB9.Signal=I2C1_SDA
PC0.GPIOParameters=GPIO_Label
PC0.GPIO_Label=DIO2
PC0.Signal=GPIO_Output
PC1.Mode=RMII
PC1.Signal=ETH_MDC
PC10.GPIOParameters=GPIO_Label
PC10.GPIO_Label=RS485_2_TX
PC10.Mode=Asynchronous
PC10.Signal=UART4_TX
PC11.GPIOParameters=GPIO_Label
PC11.GPIO_Label=RS485_2_RX
PC11.Mode=Asynchronous
PC11.Signal=UART4_RX
PC12.Mode=Full_Duplex_Master
PC12.Signal=SPI6_SCK
PC2_C.GPIOParameters=GPIO_Label
PC2_C.GPIO_Label=AI2
PC2_C.Mode=IN0-Single-Ended
PC2_C.Signal=ADC3_INP0
PC3_C.GPIOParameters=GPIO_Label
PC3_C.GPIO_Label=AI1
PC3_C.Mode=IN1-Single-Ended
PC3_C.Signal=ADC3_INP1
PC4.Mode=RMII
PC4.Signal=ETH_RXD0
PC5.Mode=RMII
PC5.Signal=ETH_RXD1
PC6.GPIOParameters=GPIO_Label
PC6.GPIO_Label=QE1_A
PC6.Signal=S_TIM3_CH1
PC7.GPIOParameters=GPIO_Label
PC7.GPIO_Label=QE1_B
PC7.Signal=S_TIM3_CH2
PC8.GPIOParameters=GPIO_Label
PC8.GPIO_Label=DIO16
PC8.Signal=GPIO_Output
PC9.Mode=I2C
PC9.Signal=I2C3_SDA
PD0.GPIOParameters=GPIO_Label
PD0.GPIO_Label=QE1_I
PD0.Signal=GPIO_Output
PD1.GPIOParameters=GPIO_Label
PD1.GPIO_Label=QE2_I
PD1.Signal=GPIO_Output
PD10.GPIOParameters=GPIO_Label
PD10.GPIO_Label=DIO8
PD10.Signal=GPIO_Output
PD11.GPIOParameters=GPIO_Label
PD11.GPIO_Label=DIO9
PD11.Signal=GPIO_Output
PD12.GPIOParameters=GPIO_Label
PD12.GPIO_Label=QE2_A
PD12.Signal=S_TIM4_CH1
PD13.GPIOParameters=GPIO_Label
PD13.GPIO_Label=QE2_B
PD13.Signal=S_TIM4_CH2
PD14.GPIOParameters=GPIO_Label
PD14.GPIO_Label=DEBUG_UART_RX
PD14.Mode=Asynchronous
PD14.Signal=UART9_RX
PD15.GPIOParameters=GPIO_Label
PD15.GPIO_Label=DEBUG_UART_TX
PD15.Mode=Asynchronous
PD15.Signal=UART9_TX
PD2.GPIOParameters=GPIO_Label
PD2.GPIO_Label=QE3_I
PD2.Signal=GPIO_Output
PD3.GPIOParameters=GPIO_Label
PD3.GPIO_Label=QE4_I
PD3.Signal=GPIO_Output
PD5.GPIOParameters=GPIO_Label
PD5.GPIO_Label=UART2_TX
PD5.Mode=Asynchronous
PD5.Signal=USART2_TX
PD6.GPIOParameters=GPIO_Label
PD6.GPIO_Label=UART2_RX
PD6.Mode=Asynchronous
PD6.Signal=USART2_RX
PD7.Mode=Full_Duplex_Master
PD7.Signal=SPI1_MOSI
PD8.GPIOParameters=GPIO_Label
PD8.GPIO_Label=RS485_1_TX
PD8.Mode=Asynchronous
PD8.Signal=USART3_TX
PD9.GPIOParameters=GPIO_Label
PD9.GPIO_Label=RS485_1_RX
PD9.Mode=Asynchronous
PD9.Signal=USART3_RX
PE10.GPIOParameters=GPIO_Label
PE10.GPIO_Label=DIO4
PE10.Signal=GPIO_Output
PE11.GPIOParameters=GPIO_Label
PE11.GPIO_Label=PWM2
PE11.Signal=S_TIM1_CH2
PE12.GPIOParameters=GPIO_Label
PE12.GPIO_Label=DIO5
PE12.Signal=GPIO_Output
PE13.GPIOParameters=GPIO_Label
PE13.GPIO_Label=PWM3
PE13.Signal=S_TIM1_CH3
PE14.GPIOParameters=GPIO_Label
PE14.GPIO_Label=PWM4
PE14.Signal=S_TIM1_CH4
PE15.GPIOParameters=GPIO_Label
PE15.GPIO_Label=DIO6
PE15.Signal=GPIO_Output
PE2.GPIOParameters=GPIO_Label
PE2.GPIO_Label=ETH_SPI_SCLK
PE2.Mode=Full_Duplex_Master
PE2.Signal=SPI4_SCK
PE4.GPIOParameters=GPIO_Label
PE4.GPIO_Label=ETH_SPI_CS
PE4.Mode=NSS_Signal_Hard_Output
PE4.Signal=SPI4_NSS
PE5.GPIOParameters=GPIO_Label
PE5.GPIO_Label=ETH_SPI_MISO
PE5.Mode=Full_Duplex_Master
PE5.Signal=SPI4_MISO
PE6.GPIOParameters=GPIO_Label
PE6.GPIO_Label=ETH_SPI_MOSI
PE6.Mode=Full_Duplex_Master
PE6.Signal=SPI4_MOSI
PE7.GPIOParameters=GPIO_Label
PE7.GPIO_Label=SEL_C
PE7.Signal=GPIO_Input
PE8.GPIOParameters=GPIO_Label
PE8.GPIO_Label=SEL_D
PE8.Signal=GPIO_Input
PE9.GPIOParameters=GPIO_Label
PE9.GPIO_Label=PWM1
PE9.Signal=S_TIM1_CH1
PF0.Mode=I2C
PF0.Signal=I2C2_SDA
PF1.Mode=I2C
PF1.Signal=I2C2_SCL
PF10.GPIOParameters=GPIO_Label
PF10.GPIO_Label=AI3
PF10.Mode=IN6-Single-Ended
PF10.Signal=ADC3_INP6
PF11.GPIOParameters=GPIO_Label
PF11.GPIO_Label=QE4_A
PF11.Mode=Encoder_Interface
PF11.Signal=TIM24_CH1
PF12.GPIOParameters=GPIO_Label
PF12.GPIO_Label=QE4_B
PF12.Signal=S_TIM24_CH2
PF13.GPIOParameters=GPIO_Label
PF13.GPIO_Label=DIO3
PF13.Signal=GPIO_Output
PF14.Mode=I2C
PF14.Signal=I2C4_SCL
PF15.Mode=I2C
PF15.Signal=I2C4_SDA
PF2.GPIOParameters=GPIO_Label
PF2.GPIO_Label=DIO1
PF2.Signal=GPIO_Output
PF3.GPIOParameters=GPIO_Label
PF3.GPIO_Label=AI10
PF3.Mode=IN5-Single-Ended
PF3.Signal=ADC3_INP5
PF4.GPIOParameters=GPIO_Label
PF4.GPIO_Label=AI9
PF4.Mode=IN9-Single-Ended
PF4.Signal=ADC3_INP9
PF5.GPIOParameters=GPIO_Label
PF5.GPIO_Label=AI8
PF5.Mode=IN4-Single-Ended
PF5.Signal=ADC3_INP4
PF6.GPIOParameters=GPIO_Label
PF6.GPIO_Label=AI7
PF6.Mode=IN8-Single-Ended
PF6.Signal=ADC3_INP8
PF7.GPIOParameters=GPIO_Label
PF7.GPIO_Label=AI6
PF7.Mode=IN3-Single-Ended
PF7.Signal=ADC3_INP3
PF8.GPIOParameters=GPIO_Label
PF8.GPIO_Label=AI5
PF8.Mode=IN7-Single-Ended
PF8.Signal=ADC3_INP7
PF9.GPIOParameters=GPIO_Label
PF9.GPIO_Label=AI4
PF9.Mode=IN2-Single-Ended
PF9.Signal=ADC3_INP2
PG0.GPIOParameters=GPIO_Label
PG0.GPIO_Label=SEL_A
PG0.Signal=GPIO_Input
PG1.GPIOParameters=GPIO_Label
PG1.GPIO_Label=SEL_B
PG1.Signal=GPIO_Input
PG10.Mode=NSS_Signal_Hard_Output
PG10.Signal=SPI1_NSS
PG11.Mode=Full_Duplex_Master
PG11.Signal=SPI1_SCK
PG12.GPIOParameters=GPIO_Label
PG12.GPIO_Label=QE3_A
PG12.Mode=Encoder_Interface
PG12.Signal=TIM23_CH1
PG13.GPIOParameters=GPIO_Label
PG13.GPIO_Label=QE3_B
PG13.Signal=S_TIM23_CH2
PG14.Mode=Full_Duplex_Master
PG14.Signal=SPI6_MOSI
PG2.GPIOParameters=GPIO_Label
PG2.GPIO_Label=DIO10
PG2.Signal=GPIO_Output
PG3.GPIOParameters=GPIO_Label
PG3.GPIO_Label=DIO11
PG3.Signal=GPIO_Output
PG4.GPIOParameters=GPIO_Label
PG4.GPIO_Label=DIO12
PG4.Signal=GPIO_Output
PG5.GPIOParameters=GPIO_Label
PG5.GPIO_Label=DIO13
PG5.Signal=GPIO_Output
PG6.GPIOParameters=GPIO_Label
PG6.GPIO_Label=DIO14
PG6.Signal=GPIO_Output
PG7.GPIOParameters=GPIO_Label
PG7.GPIO_Label=DIO15
PG7.Signal=GPIO_Output
PG8.Mode=NSS_Signal_Hard_Output
PG8.Signal=SPI6_NSS
PG9.Mode=Full_Duplex_Master
PG9.Signal=SPI1_MISO
PH0-OSC_IN.Mode=HSE-External-Oscillator
PH0-OSC_IN.Signal=RCC_OSC_IN
PH1-OSC_OUT.Mode=HSE-External-Oscillator
PH1-OSC_OUT.Signal=RCC_OSC_OUT
RCC.HSE_VALUE=8000000
RCC.SYSCLKFreq_VALUE=64000000
board=custom

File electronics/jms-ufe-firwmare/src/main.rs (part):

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  digital_out: [gpio::ErasedPin<gpio::Output<gpio::PushPull>>; 4],
  adc1: Adc<ADC1, adc::Enabled>,
  analog_in: (
    gpio::gpioa::PA3<gpio::Analog>,
    gpio::gpioc::PC0<gpio::Analog>,
    gpio::gpiob::PB1<gpio::Analog>,
    gpio::gpioa::PA6<gpio::Analog>,
  ),
  analog_out: (dac::C1<DAC, dac::Enabled>, dac::C2<DAC, dac::Enabled>),
}
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    let gpiof = ctx.device.GPIOF.split(ccdr.peripheral.GPIOF);
    let gpiog = ctx.device.GPIOG.split(ccdr.peripheral.GPIOG);

    let mut led = gpiob.pb0.into_push_pull_output();
    led.set_low();

    let rmii_ref_clk = gpioa.pa1.into_alternate();
    let rmii_mdio = gpioa.pa2.into_alternate();
    let rmii_mdc = gpioc.pc1.into_alternate();
    let rmii_crs_dv = gpioa.pa7.into_alternate();
    let rmii_rxd0 = gpioc.pc4.into_alternate();
    let rmii_rxd1 = gpioc.pc5.into_alternate();
    let rmii_tx_en = gpiog.pg11.into_alternate();
    let rmii_txd0 = gpiog.pg13.into_alternate();
    let rmii_txd1 = gpiob.pb13.into_alternate();

    /* Generate MAC Address */
    let uid = Uid::read();
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    let (dac1, dac2) = ctx
      .device
      .DAC
      .dac((gpioa.pa4, gpioa.pa5), ccdr.peripheral.DAC12);
    let dac1 = dac1.calibrate_buffer(&mut delay).enable();
    let dac2 = dac2.calibrate_buffer(&mut delay).enable();

    // Initialise DMX512
    // let mut dmx_tx_pin = gpiod.pd5.into_push_pull_output().speed(gpio::Speed::VeryHigh);
    let dmx_tx_pin = gpiod.pd5.into_alternate();
    let dmx_rx_pin = gpiod.pd6.into_alternate();
    let mut dmx_rts_pin = gpiod
      .pd4
      .into_push_pull_output()
      .speed(gpio::Speed::VeryHigh);

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        net,
        devices: IODevices {
          digital_in: [
            gpiof.pf3.into_pull_up_input().erase(),
            gpiod.pd15.into_pull_up_input().erase(),
            gpiod.pd14.into_pull_up_input().erase(),
            gpiob.pb5.into_pull_up_input().erase(),
          ],
          digital_out: [
            led.erase(),
            gpiob.pb14.into_push_pull_output().erase(),
            gpioe.pe1.into_push_pull_output().erase(),
            gpioe.pe0.into_push_pull_output().erase(),
          ],
          adc1,
          analog_in: (
            gpioa.pa3.into_analog(),
            gpioc.pc0.into_analog(),
            gpiob.pb1.into_analog(),
            gpioa.pa6.into_analog(),
          ),
          analog_out: (dac1, dac2),
        },
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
